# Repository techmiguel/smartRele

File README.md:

# SmartRele · rele-esp12f

**Single-channel Wi-Fi relay module based on the ESP-12F (ESP8266) for 110–120 VAC mains.**

A 2-layer, **66.5 × 49 mm** board that switches a mains load of up to **10 A** from an ESP-12F. It is powered directly from the mains through an isolated HLK-PM01 supply and integrates input protection (time-lag fuse and varistor), a 16 A Omron G5RL power relay, status indicators and a programming header. All components sit on the top side, and the board is ready to be ordered **fully assembled from JLCPCB** (SMD and THT), with no hand soldering.

> [!WARNING]
> This design operates at **mains voltage**. Assembly, testing and installation must be carried out by qualified people. Read the [Safety](#safety) section before connecting the board.

---

## Table of contents
- [Features](#features)
- [Specifications](#specifications)
- [Architecture](#architecture)
- [Connectors and pinout](#connectors-and-pinout)
- [Repository layout](#repository-layout)
- [Manufacturing and assembly](#manufacturing-and-assembly)
- [Firmware](#firmware)
- [First firmware flashing](#first-firmware-flashing)
- [Enclosure](#enclosure)
- [Design verification](#design-verification)
- [Safety](#safety)
- [Documentation](#documentation)
- [License](#license)

## Features
- **ESP-12F** with its PCB antenna overhanging a cut-out in the top-right corner: no copper and no FR-4 below it, as the Espressif hardware design guidelines recommend.
- **Omron G5RL-1A-E-HR relay** (SPST-NO, 16 A / 250 VAC) with 8 mm coil-to-contact separation (reinforced insulation per the manufacturer).
- **Strict mains / low-voltage zoning** enforced by custom design rules: 4 mm between mains and low voltage, 2 mm between mains nets. Measured minimum clearance: 4.35 mm.
- **Duplicated power path** on both sides (2 × 2.5 mm, 35 µm), sized for 10 A with a ~12 °C temperature rise (IPC-2221).
- **Input protection**: T500mA time-lag fuse (protects the supply) and 07D221K varistor.
- **Robust start-up**: RC delay on EN and RST, 10 µF + 100 nF decoupling next to the module, and the relay held open during reset.
- **Indicators** for relay (red) and Wi-Fi (blue); user/boot (GPIO0) and reset push buttons.
- **Programming** through a 2×3 header powered at 5 V; OTA updates afterwards.
- **Complete manufacturing package**: Gerbers, drill files, BOM and CPL ready for JLCPCB, with 3D models for every part.
- **3D-printable enclosure**, parametric and checked against the 3D model of the assembled board.

## Specifications

| Parameter | Value |
|---|---|
| Input voltage | 110–120 VAC, 50/60 Hz |
| Maximum load | 10 A resistive (trace limit; relay 16 A, terminal block 18 A) |
| Contact | SPST-NO, switches the line (L) |
| On-board supply | HLK-PM01, 5 V / 600 mA, isolated |
| Regulator | AMS1117-3.3 |
| Microcontroller | ESP8266 (ESP-12F module), Wi-Fi 802.11 b/g/n |
| Protection | F1 T500mA 250 V (supply branch) · RV1 07D221K |
| PCB | 66.5 × 49 × 1.6 mm, 2 layers, 35 µm copper; 7.6 × 18.7 mm cut-out under the antenna |
| Assembly | Single-sided; 32 components, all factory-assembled |
| Mounting holes | 2 × M2 (MH1, MH2), in the low-voltage zone |

The full datasheet, with test conditions and the source of each value, is in [`docs/rele-esp12f_datasheet_user_guide.pdf`](docs/rele-esp12f_datasheet_user_guide.pdf).

## Architecture

```
 Power      J1:L ──────────► K1 contact (COM → NO) ──────────► J1:OUT ──► load

 Supply     J1:L ── F1 ── L_F ──► PS1 HLK-PM01 ──► +5 V ── U1 AMS1117 ──► +3.3 V ──► U2 ESP-12F
                          RV1 between L_F and N

 Control    +5 V ── K1 coil (D1 flyback diode) ── Q1 SS8050 ── GND
                                                   ▲
                                        GPIO5 (U2) ── R6 1 kΩ
```

- **Mains zone** (bottom left): J1, F1, RV1, K1 and the PS1 input.
- **Low-voltage zone** (right): U1 and its capacitors, relay driver, LEDs, push buttons, J3 and mounting holes. GND planes on both sides, restricted to this zone.
- **Top strip**: PS1 on the left and the ESP-12F with its antenna over the corner cut-out on the right edge.

The full schematic is in [`docs/schematic.pdf`](docs/schematic.pdf).

## Connectors and pinout

### J1 — Mains terminal block (3 poles, 5.08 mm pitch)
| Pin | Signal | Function |
|:-:|---|---|
| 1 | N | Neutral |
| 2 | OUT | Switched output to the load |
| 3 | L | Line input |

### J3 — Programming (2×3 header, 2.54 mm pitch)
```
 IO0   TX   GND(1)
 RST   RX   5V
```
Pin 1 (square pad) = GND; pin 2 = 5 V. Labeled on the silkscreen.

### ESP-12F
| GPIO | Function |
|---|---|
| GPIO5 | Relay (SS8050, R6 1 kΩ, R7 10 kΩ to GND) and relay LED (D2) |
| GPIO4 | Wi-Fi LED (D3) |
| GPIO0 | Push button SW1 (flashing mode / application use), 10 kΩ to 3.3 V |
| GPIO2 | 10 kΩ to 3.3 V (boot strap) |
| GPIO15 | 10 kΩ to GND (boot strap) |
| EN, RST | 10 kΩ to 3.3 V + 100 nF to GND; RST also to SW2 |

## Repository layout

```
.
├── rele-esp12f.kicad_pro      KiCad 10 project
├── rele-esp12f.kicad_sch      Schematic
├── rele-esp12f.kicad_pcb      PCB layout
├── rele-esp12f.kicad_dru      Custom design rules (mains isolation)
├── 3dmodels/                  STEP models missing from the KiCad library (K1, F1, SW1/SW2)
├── fabrication/               Production package for JLCPCB
│   ├── gerbers/               Gerbers and drill files (Excellon)
│   ├── gerbers_JLCPCB.zip     Gerbers + drill files + CPL, ready to upload
│   ├── BOM_JLCPCB.csv         Bill of materials with LCSC part numbers
│   └── CPL_JLCPCB.csv         Component placement list
├── docs/
│   ├── schematic.pdf
│   ├── rele-esp12f_datasheet_user_guide.pdf
│   ├── pcb_top.png · pcb_bottom.png
│   └── datasheets/            Datasheets of the key components
├── firmware/                  ESP8266 firmware (PlatformIO, Arduino core)
├── enclosure/                 3D-printable enclosure (FreeCAD, STEP, STL)
├── scripts/                   PDF datasheet generator
├── CHANGELOG.md
└── LICENSE
```

The custom 3D models are referenced through `${KIPRJMOD}/3dmodels/`, so the project opens without any extra path configuration.

## Manufacturing and assembly

1. Upload [`fabrication/gerbers_JLCPCB.zip`](fabrication/gerbers_JLCPCB.zip) to JLCPCB (2 layers, 1.6 mm).
2. Enable **PCB Assembly** (top side) and upload [`BOM_JLCPCB.csv`](fabrication/BOM_JLCPCB.csv) and [`CPL_JLCPCB.csv`](fabrication/CPL_JLCPCB.csv).
3. Before paying, check in the JLCPCB viewer that:
   - U2 and K1 sit on their pads;
   - the J1 wire entry faces the board edge;
   - J3 pin 1 lands on the square pad (GND);
   - every BOM line has a part selected.

THT parts are wave-soldered. The CPL uses the **pad center** (JLCPCB convention), not the body center; for U2 and K1 they differ. The drill holes of J1 (Ø1.5 mm) and RV1 (Ø1.0 mm) are matched to the actual parts.

### Power and THT components

| Ref. | Part | LCSC | Notes |
|---|---|---|---|
| PS1 | Hi-Link HLK-PM01 | C209903 | Isolated 5 V supply |
| K1 | Omron G5RL-1A-E-HR DC5 | C113250 | SPST-NO 16 A; 5 V coil, 80 mA |
| F1 | Reomax MTS0500A, T500mA 250 V | C2762401 | Time-lag, due to the PS1 inrush current |
| RV1 | Varistor 07D221K | C49072913 | For 110–120 VAC |
| C1 | 470 µF 10 V | C112505 | |
| J1 | KANGNEX WJ500V-5.08-3P | C72334 | 250 V / 18 A |
| J3 | 2×3 header, 2.54 mm | C65114 | Only used for the first flashing |

The full list is in the [BOM](fabrication/BOM_JLCPCB.csv).

### Regenerating the production files

With `kicad-cli` (KiCad 10), from the repository root:

```bash
kicad-cli pcb export gerbers --layers F.Cu,B.Cu,F.SilkS,B.SilkS,F.Mask,B.Mask,F.Paste,Edge.Cuts -o fabrication/gerbers/ rele-esp12f.kicad_pcb
```

```bash
kicad-cli pcb export drill --format excellon --excellon-units mm --excellon-separate-th --excellon-zeros-format decimal -o fabrication/gerbers/ rele-esp12f.kicad_pcb
```

```bash
kicad-cli pcb render --side top -w 1592 -h 904 --background opaque --quality basic --zoom 0.9954 -o docs/pcb_top.png rele-esp12f.kicad_pcb
```

```bash
kicad-cli pcb render --side bottom -w 1592 -h 904 --background opaque --quality basic --zoom 0.9954 -o docs/pcb_bottom.png rele-esp12f.kicad_pcb
```

These explicit options are needed because the plot settings stored in the board produce `.gbr` extensions and an unnecessary B.Paste layer. The ZIP contains the 11 files in `fabrication/gerbers/` plus `CPL_JLCPCB.csv`.

## Firmware

The [`firmware/`](firmware/) folder holds the board's own firmware (PlatformIO, Arduino core for ESP8266). The relay is controlled over Wi-Fi from a built-in web page or a JSON REST API, and from anywhere on the Internet through a Telegram bot:

- manual on / off;
- state-change timer (turn on, off or toggle after 1 s – 7 days);
- cyclic ON/OFF routine (on for one period, off for another, repeated);
- up to 16 weekly schedules synchronised over NTP, with a configurable time zone;
- Telegram bot (optional): remote control and notifications with no server and no port forwarding, so it also works on a phone hotspot or behind CGNAT.

On first boot it opens the `SmartRele-XXXXXX` setup access point; holding SW1 for 8 s erases the Wi-Fi settings. Setup, behaviour, API and security notes are in [`firmware/README.md`](firmware/README.md).

## First firmware flashing

1. **Disconnect the board from mains.**
2. Connect a USB-serial adapter with **3.3 V logic** to J3: TX↔RX, RX↔TX, GND, and its **5 V (VBUS)** output to the 5V pin.
3. Hold SW1 (GPIO0) while pressing and releasing SW2 (RST) to enter flashing mode.
4. Flash the firmware (`pio run -e esp12f -t upload` from `firmware/`). Later updates are done over the air (OTA).

J3 is powered at 5 V rather than 3.3 V for two reasons. The internal output-to-input diode of the AMS1117 would make the adapter also feed the 5 V rail. In addition, the 3.3 V pin of a typical adapter cannot supply the current peaks the ESP8266 draws while calibrating its radio.

Third-party firmware also works: the [datasheet](docs/rele-esp12f_datasheet_user_guide.pdf) includes example configurations for Tasmota and ESPHome.

## Enclosure

The [`enclosure/`](enclosure/) folder contains a two-part enclosure (base and screwed lid) for 3D printing in PETG or ASA/ABS. It is generated by a parametric FreeCAD script, and its interference with the 3D model of the assembled board is zero. Design, printing and assembly details are in [`enclosure/README.md`](enclosure/README.md).

## Design verification

Results with `kicad-cli` 10.0.5, with all zones refilled:

| Check | Errors | Warnings | Warning details |
|---|:-:|:-:|---|
| DRC | **0** | 31 | 23 footprints modified from the library (J1/RV1 drills and custom 3D models; pads otherwise identical); 8 silkscreen items clipped by the edge (PS1/J1 at the rounded corners, U2 outline over the antenna cut-out) |
| Schematic ↔ PCB parity | **0** | 0 | |
| ERC | **0** | 6 | Embedded symbols that differ from the KiCad 10 library (pinout checked against the datasheets) |
| Unconnected pads | **0** | — | |

None of the warnings affects manufacturing. The [kicad-verify](https://github.com/techmiguel/kicad-verify) gate (`verification/pcb/`) also checks the pinout of U1, U2, Q1, PS1, K1 and D1 against their datasheets, the mounting holes against the enclosure, and the consistency of the Gerbers, drill files, BOM and CPL with the board. Measured clearances: mains copper ↔ low voltage ≥ 4.35 mm on both sides; mains copper ↔ board edge ≥ 2.0 mm.

## Safety

- **110–120 VAC mains.** The 07D221K varistor is rated for that voltage. For 230 VAC it must be replaced (e.g. with a 07D471K). F1 is suitable for both voltages.
- **The load current does not flow through F1**, which only protects the supply. Install a circuit breaker or fuse of **≤ 10 A** upstream, dedicated to this output. An on-board fuse would not have enough breaking capacity for a mains short circuit.
- **Never connect J3 while the board is connected to mains.**
- Mount the board in an **insulating enclosure**: mains copper is 2 mm from the board edge.
- Use only **MH1 and MH2** (low-voltage zone) for metal hardware: M2 screws with a head or washer of Ø ≤ 5 mm.
- The printed enclosure provides mechanical and contact protection, but it is **not certified**. For a permanent installation, print it in a flame-retardant material or place it inside an approved electrical junction box.

## Documentation

| Document | Contents |
|---|---|
| [Datasheet and user guide](docs/rele-esp12f_datasheet_user_guide.pdf) | Specifications, operation, installation and design rationale |
| [Schematic](docs/schematic.pdf) | Full schematic in PDF |
| [Datasheets](docs/datasheets/) | Omron G5RL, AMS1117, ESP8266EX, ESP-WROOM-02 and the Espressif hardware design guidelines |
| [Changelog](CHANGELOG.md) | Hardware revisions and the rationale behind each change |
| [Enclosure](enclosure/README.md) | Enclosure design, printing and assembly |

The datasheet is regenerated with `python scripts/generate_datasheet.py` (requires ReportLab, PyMuPDF, Pillow and `kicad-cli`).

## License

Hardware released under the **CERN Open Hardware Licence v2 – Weakly Reciprocal** ([CERN-OHL-W-2.0](LICENSE)).

Inspired by [aman983/ESP-01S_Relay_Module](https://github.com/aman983/ESP-01S_Relay_Module). This is a new design and contains no files from the original.

---

© 2026 [@techmigue](https://github.com/techmiguel)

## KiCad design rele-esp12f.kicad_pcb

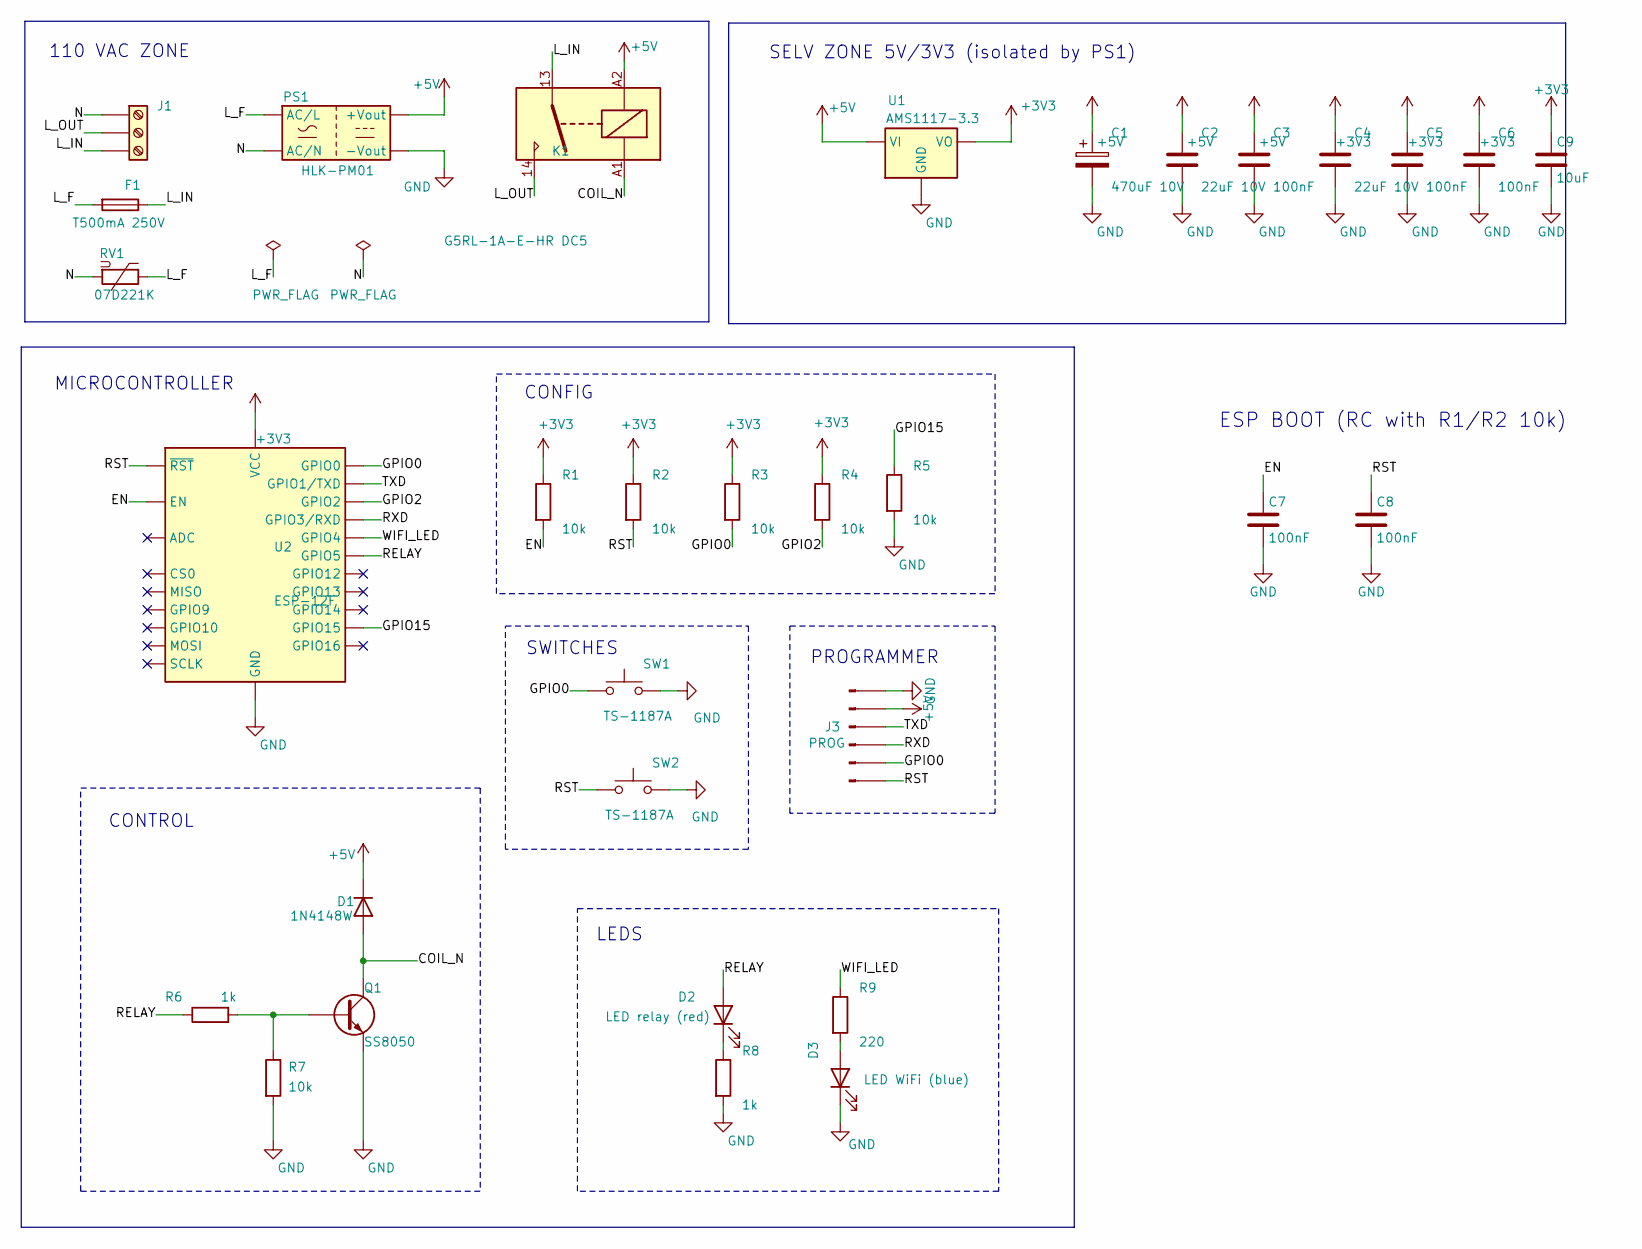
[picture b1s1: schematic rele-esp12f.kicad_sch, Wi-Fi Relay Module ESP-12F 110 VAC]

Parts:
C1: 470uF 10V; CP_Radial_D6.3mm_P2.50mm; MPN ERR1AM471E11OT; LCSC C112505
C2, C4: 22uF 10V; C_0805_2012Metric; MPN CL21A226MAQNNNE; LCSC C45783
C3, C5, C6, C7, C8: 100nF; C_0603_1608Metric; MPN CC0603KRX7R9BB104; LCSC C14663
C9: 10uF; C_0603_1608Metric; MPN CL10A106KP8NNNC; LCSC C19702
D1: 1N4148W; D_SOD-123; MPN 1N4148W; LCSC C81598
D2: LED relay (red); LED_0603_1608Metric; MPN KT-0603R; LCSC C2286
D3: LED WiFi (blue); LED_0603_1608Metric; MPN GL0603UB01; LCSC C51933294
F1: T500mA 250V; Fuse_Littelfuse_395Series; MPN MTS0500A; LCSC C2762401
J1: N / L_OUT / L_IN; TerminalBlock_Phoenix_MKDS-1,5-3-5.08_1x03_P5.08mm_Horizont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; MPN WJ500V-5.08-03P-14-00A; LCSC C72334
J3: PROG; PinHeader_2x03_P2.54mm_Vertical; MPN 2.54-2*3P Pin header; LCSC C65114
K1: G5RL-1A-E-HR DC5; Relay_SPST_Omron_G2RL-1A-E; MPN G5RL-1A-E-HR DC5; LCSC C113250
PS1: HLK-PM01; Converter_ACDC_Hi-Link_HLK-PMxx; MPN HLK-PM01; LCSC C209903
Q1: SS8050; SOT-23; MPN SS8050; LCSC C2150
R1, R2, R3, R4, R5, R7: 10k; R_0603_1608Metric; MPN 0603WAF1002T5E; LCSC C25804
R6, R8: 1k; R_0603_1608Metric; MPN 0603WAF1001T5E; LCSC C21190
R9: 220; R_0603_1608Metric; MPN 0603WAF2200T5E; LCSC C22962
RV1: 07D221K; RV_Disc_D7mm_W3.4mm_P5mm; MPN 07D221K; LCSC C49072913
SW1, SW2: TS-1187A; SW_Push_1P1T_XKB_TS-1187A; MPN TS-1187A-B-A-B; LCSC C318884
U1: AMS1117-3.3; SOT-223-3_TabPin2; MPN AMS1117-3.3; LCSC C6186
U2: ESP-12F; ESP-12E; MPN ESP-12F; LCSC C82891

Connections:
+3V3: C4.1, C5.1, C6.1, C9.1, R1.1, R2.1, R3.1, R4.1, U1.2 (VO), U2.8 (VCC)
+5V: C1.1, C2.1, C3.1, D1.1 (K), J3.2, K1.A2, PS1.4 (+Vout), U1.3 (VI)
/COIL_N: D1.2 (A), K1.A1, Q1.3 (C)
/EN: C7.1, R1.2, U2.3 (EN)
/GPIO0: J3.5, R3.2, SW1.1, U2.18 (GPIO0)
/GPIO2: R4.2, U2.17 (GPIO2)
/GPIO15: R5.1, U2.16 (GPIO15)
/L_F: F1.2, PS1.1 (AC/L), RV1.1
/L_IN: F1.1, J1.3, K1.13
/L_OUT: J1.2, K1.14
/N: J1.1, PS1.2 (AC/N), RV1.2
/RELAY: D2.2 (A), R6.1, U2.20 (GPIO5)
/RST: C8.1, J3.6, R2.2, SW2.1, U2.1 (~RST)
/RXD: J3.4, U2.21 (GPIO3/RXD)
/TXD: J3.3, U2.22 (GPIO1/TXD)
/WIFI_LED: R9.1, U2.19 (GPIO4)
GND: C1.2, C2.2, C3.2, C4.2, C5.2, C6.2, C7.2, C8.2, C9.2, D3.1 (K), J3.1, PS1.3 (-Vout), Q1.2 (E), R5.2, R7.2, R8.2, SW1.2, SW2.2, U1.1 (GND), U2.15 (GND)
unnamed: D2.1 (K), R8.1
unnamed: D3.2 (A), R9.2
unnamed: Q1.1 (B), R6.2, R7.1

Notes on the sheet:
PROGRAMMER
MICROCONTROLLER
110 VAC ZONE
CONFIG
SELV ZONE 5V/3V3 (isolated by PS1)
LEDS
SWITCHES
CONTROL
ESP BOOT (RC with R1/R2 10k)

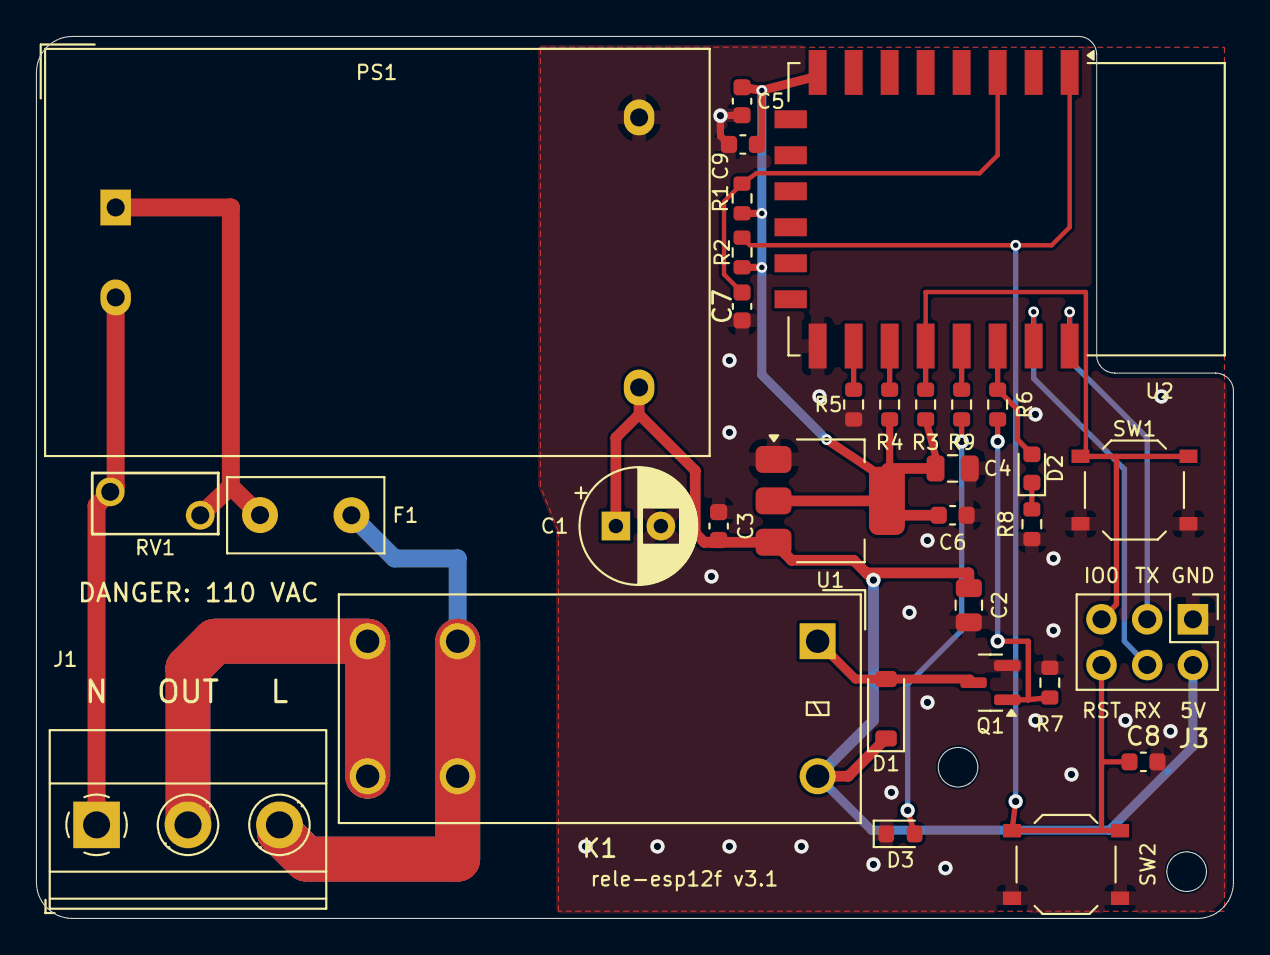
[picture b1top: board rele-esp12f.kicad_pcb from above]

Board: 2 copper layers, 66.5 x 49.0 mm, 34 parts (0 on the bottom side), 20 nets.

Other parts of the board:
MH1, MH2: M2; MountingHole_2.2mm_M2

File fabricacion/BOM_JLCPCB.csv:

Comment,Designator,Footprint,LCSC Part #
22uF 10V,"C2,C4",C_0805_2012Metric,C45783
10uF 10V X5R,C9,C_0603_1608Metric,C19702
100nF,"C3,C5,C6,C7,C8",C_0603_1608Metric,C14663
1N4148W,D1,D_SOD-123,C81598
LED relay (rojo),D2,LED_0603_1608Metric,C2286
LED WiFi (azul),D3,LED_0603_1608Metric,C51933294
SS8050,Q1,SOT-23,C2150
10k,"R1,R2,R3,R4,R5,R7",R_0603_1608Metric,C25804
1k,"R6,R8",R_0603_1608Metric,C21190
220,R9,R_0603_1608Metric,C22962
TS-1187A,"SW1,SW2",SW_Push_1P1T_XKB_TS-1187A,C318884
AMS1117-3.3,U1,SOT-223-3_TabPin2,C6186
470uF 10V,C1,CP_Radial_D6.3mm_P2.50mm,C112505
T500mA 250V (Reomax MTS0500A; time-lag),F1,Fuse_Littelfuse_395Series,C2762401
"G5RL-1A-E-HR DC5 (Omron, 16 A, SPST-NO)",K1,Relay_SPST_Omron_G2RL-1A-E,C113250
HLK-PM01,PS1,Converter_ACDC_Hi-Link_HLK-PMxx,C209903
07D221K,RV1,RV_Disc_D7mm_W3.4mm_P5mm,C49072913
ESP-12F,U2,ESP-12E,C82891
N / L_OUT / L_IN (borna 3P 5.08 mm),J1,"TerminalBlock_Phoenix_MKDS-1,5-3-5.08_1x03_P5.08mm_Horizontal",C72334
PROG (header 2x3 2.54 mm),J3,PinHeader_2x03_P2.54mm_Vertical,C65114

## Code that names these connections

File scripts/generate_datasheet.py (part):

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    arrow(g, [362, 196, 392, 196], ACC)        ; lbl(g, 365, 199, '+3V3', 6.4, ACC)
    arrow(g, [276, 196, 276, 80, 266, 80], ACC); lbl(g, 270, 92, 'coil', 5.8, ACC)
    arrow(g, [292, 62, 266, 62], ACC)          ; lbl(g, 268, 52, 'COIL_N', 5.8, ACC)
    arrow(g, [392, 124, 378, 124, 378, 70, 362, 70], ACC); lbl(g, 380, 96, 'GPIO5', 6.0, ACC)
    arrow(g, [378, 130, 362, 130], ACC)        ; lbl(g, 364, 150, 'GPIO5/4', 5.8, ACC)
    arrow(g, [424, 82, 424, 112], ACC)         ; lbl(g, 427, 92, 'GPIO0 / RST', 5.8, ACC)
    arrow(g, [Wd - 14, 34, Wd - 14, 112], ACC) ; lbl(g, Wd - 17, 70, 'UART', 5.8, ACC, anchor='end')
    d.add(g)
    return d
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        'ESP8266EX: Xtensa L106 CPU at 80/160 MHz, Wi-Fi 802.11 b/g/n, +20 dBm in 802.11b [D].',
        'Safe boot state: the relay stays open during reset and boot (pull-down resistor on the transistor base).',
        'Indicators: red relay-status LED (hardwired) and blue Wi-Fi LED (firmware-controlled).',
        'Local push button SW1 (GPIO0, also used to enter flashing mode) and reset push button SW2.',
        'Programming header J3 (2×3, 2.54 mm) powered at 5 V from the USB-serial adapter; later updates over the air (OTA).',
        '2-layer FR-4 PCB, 1.6 mm, 35 µm copper, 66.5 × 49 mm. All components on the top side.',
    ]))
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        'The on-board resistors select normal boot from flash; SW1 forces UART flashing mode.'))
    A(table([
        ['Pin', 'Net', 'Components', 'Level at boot', 'Effect'],
        ['GPIO15', '/GPIO15', 'R5 10 k to GND', '0', 'Must be 0 to boot from flash or UART.'],
        ['GPIO2', '/GPIO2', 'R4 10 k to 3V3', '1', 'Must be 1.'],
        ['GPIO0', '/GPIO0', 'R3 10 k to 3V3; SW1 to GND; J3-5', '1 (0 with SW1)', '1 = boot from flash; 0 = UART flashing mode.'],
        ['EN (CH_PD)', '/EN', 'R1 10 k to 3V3; C7 100 nF to GND', '↑ with τ = 1 ms', 'Enables the chip once VCC has settled.'],
        ['RST', '/RST', 'R2 10 k to 3V3; C8 100 nF; SW2 to GND; J3-6', '↑ with τ = 1 ms', 'External reset; SW2 restarts the module.'],
    ], [1.4, 1.4, 3.6, 1.8, 4.6]))
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        'after VDD33 (t<sub>3</sub>, t<sub>5</sub> ≥ 0.1 ms [D]). Without capacitors, a slow ramp of the '
        '3.3 V rail can leave the chip in an undefined state.'))
    A(Paragraph('3.4 Relay driver', sH2))
    A(P('GPIO5 (net <font face="Mono">/RELAY</font>) drives the base of Q1 (SS8050, NPN) through R6 (1 kΩ). '
        'Q1 switches the low side of the coil (<font face="Mono">/COIL_N</font>); the other end is at +5 V. '
        'D1 (1N4148W) recirculates the coil current when Q1 turns off and clamps its collector to '
        '≈ 5.7 V. R7 (10 kΩ) holds the base at GND while GPIO5 is high-impedance (reset, boot, '
        'flashing): the relay <b>cannot close</b> until the firmware commands it.'))
    A(table([
        ['Quantity', 'Calculation', 'Result'],
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        ['Base current (V<sub>OH</sub> = 3.3 V)', '(3.3 − 0.75) / 1 k − 0.75 / 10 k', '2.48 mA'],
        ['Base current (V<sub>OH</sub> min. = 2.64 V)', '(2.64 − 0.75) / 1 k − 0.75 / 10 k', '1.82 mA'],
        ['Forced β (worst case)', '80 mA / 1.82 mA', '≈ 44 → saturation with ample margin (SS8050 h<sub>FE</sub> ≫ 44)'],
        ['Total GPIO5 current', 'I<sub>B</sub> + I<sub>D2</sub> ≈ 2.5 + 1.4', '≈ 3.9 mA (< 12 mA [D])'],
    ], [3.3, 4.7, 5]))
    A(P('With a plain parallel diode the coil current decays slowly and the contact opens somewhat later than '
        'the 5 ms in the datasheet (not measured). For a 10 A AC load this is acceptable; a zener in series '
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    A(Paragraph('3.5 Indicators and push buttons', sH2))
    A(table([
        ['Ref.', 'Element', 'Connection', 'Logic', 'Notes'],
        ['D2', 'Red "relay" LED', 'GPIO5 → D2 → R8 1 k → GND', 'Active high', 'In parallel with the driver: on = close command issued. ≈ 1.4 mA [E].'],
        ['D3', 'Blue "Wi-Fi" LED', 'GPIO4 → R9 220 Ω → D3 → GND', 'Active high', 'Meaning defined by the firmware. Current ≈ 1–2 mA, depends on the blue LED V<sub>F</sub> [E].'],
        ['SW1', 'TS-1187A push button', 'GPIO0 ↔ GND', 'Active low', 'Local switching in service; held during reset = flashing mode.'],
        ['SW2', 'TS-1187A push button', 'RST ↔ GND', 'Active low', 'Module reset.'],
    ], [0.8, 2.3, 3.6, 1.6, 5]))
    A(PageBreak())
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        ['2', '+5 V (input)', '5 V / VBUS'],
        ['3', 'ESP TXD', 'adapter RX'],
        ['4', 'ESP RXD', 'adapter TX'],
        ['5', 'GPIO0', 'GND to flash (or use SW1)'],
        ['6', 'RST', 'optional (or use SW2)'],
    ], [1.3, 1.6, 2.6])
    wrap = Table([[jt, jdesc]], colWidths=[75 * mm, W_FULL - 75 * mm])
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    A(Paragraph('4.3 ESP-12F pin assignment', sH2))
    A(table([
        ['Module pin', 'GPIO', 'Net', 'Direction', 'Use'],
        ['20', 'GPIO5', '/RELAY', 'Output', 'Relay K1 (via Q1) and LED D2. Active high.'],
        ['19', 'GPIO4', '/WIFI_LED', 'Output', 'LED D3. Active high.'],
        ['18', 'GPIO0', '/GPIO0', 'Input', 'Push button SW1 (active low, pull-up R3). Strapping pin.'],
        ['22', 'GPIO1 / TXD', '/TXD', 'Output', 'UART0 TX → J3-3. Firmware log at 115,200 bit/s (typical).'],
        ['21', 'GPIO3 / RXD', '/RXD', 'Input', 'UART0 RX ← J3-4.'],
        ['17', 'GPIO2', '/GPIO2', '—', 'Pull-up R4. Strapping pin. Usable by the firmware with care (on many ESP-12F modules it drives the on-module blue LED, active low [F]).'],
        ['16', 'GPIO15', '/GPIO15', '—', 'Pull-down R5. Strapping pin. Do not use.'],
        ['1 · 3', 'RST · EN', '/RST · /EN', 'Input', 'Reset (SW2, J3-6) and enable, with a 1 ms RC.'],
        ['4, 5, 6, 7', 'GPIO16, 14, 12, 13', '—', '—', 'Not connected. Only reachable by soldering to the module castellations.'],
        ['2', 'ADC (TOUT)', '—', '—', 'Not connected.'],
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    A(code('{"NAME":"rele-esp12f","GPIO":[32,0,0,0,544,224,0,0,0,0,0,0,0,0],"FLAG":0,"BASE":18}'))
    A(table([
        ['Position', 'GPIO', 'Code', 'Tasmota function'],
        ['1', 'GPIO0', '32', 'Button1 (SW1)'],
        ['5', 'GPIO4', '544', 'LedLink (D3, shows Wi-Fi/MQTT connection)'],
        ['6', 'GPIO5', '224', 'Relay1 (K1 and D2)'],
        ['others', '—', '0', 'Unused (GPIO1/3 remain the UART for logging)'],
    ], [1.3, 1.3, 1.3, 8]))
    A(P('Recommended console settings: <font face="Mono">PowerOnState 0</font> (relay open after a power '
        'outage) or <font face="Mono">PowerOnState 3</font> (restore the last state), and <font face="Mono">SetOption1 1</font> '
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ota:
  - platform: esphome
status_led:
  pin: GPIO4                    # D3, active high
switch:
  - platform: gpio
    id: relay
    name: "Relay"
    pin: GPIO5                  # Q1 -> K1, and LED D2
    restore_mode: RESTORE_DEFAULT_OFF
binary_sensor:
  - platform: gpio
    name: "Button SW1"
    pin:
      number: GPIO0
      inverted: true            # active low, external pull-up R3
    filters:
      - delayed_on: 30ms        # debounce
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'''))
    A(callout('note', 'Custom firmware (Arduino / PlatformIO)', [
        'Board: "Generic ESP8266 Module" or "NodeMCU 1.0 (ESP-12E)"; 4 MB flash, DOUT or DIO mode.',
        'Configure GPIO5 as an output and write LOW first thing in <font face="Mono">setup()</font>.',
        'Read GPIO0 as a debounced input. Do not use GPIO6–11, and do not turn GPIO15/GPIO2 into outputs that could be left at the wrong level on reset.',
        'Include OTA updates from the first version: once the board is installed, J3 can no longer be used.']))
    A(PageBreak())

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    A(Paragraph('13.1 Indicators', sH2))
    A(table([
        ['Indicator', 'State', 'Meaning'],
        ['Red LED (D2)', 'On', 'The firmware commands the relay to close (GPIO5 high). It is wired in parallel with the driver, so it reflects the command, not the mechanical position of the contact.'],
        ['Red LED (D2)', 'Off', 'Relay open; also during boot and flashing.'],
        ['Blue LED (D3)', 'Firmware-defined', 'Tasmota (LedLink): blinks while looking for Wi-Fi/MQTT, off once connected (configurable with LedState). ESPHome (status_led): blinks on error or warning, off when all is well.'],
        ['Audible click', 'When switching', 'K1 contact closing or opening. If the red LED changes without a click, see §15.'],
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    A(table([
        ['Symptom', 'Probable cause', 'Check / solution'],
        ['With mains: no LED, not visible on the Wi-Fi network', 'F1 open, PS1 faulty, terminal block badly wired or no firmware.', 'Without mains, power from J3: if it works, the fault is in the mains zone (F1, RV1, PS1). Check F1 continuity de-energized.'],
        ['Firmware does not start; the serial console shows "boot mode:(1,x)"', 'GPIO0 low at boot.', 'SW1 stuck or IO0 wire to GND on J3. Release it and press SW2.'],
        ['esptool does not connect ("Failed to connect")', 'Not in flashing mode; TX/RX not crossed; port or drivers.', 'Repeat §10.2; cross TX↔RX; try 115,200 bit/s; check the COM port.'],
        ['Resets when Wi-Fi connects or the relay switches', 'Insufficient supply.', 'Via J3: use the adapter 5 V, not 3.3 V, and a short USB cable. With mains: check C1/C9 and the PS1 output.'],
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

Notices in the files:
README.md:
License: CERN-OHL-W-2.0
rele-esp12f.kicad_sch:
Hardware: CERN-OHL-W v2
scripts/generate_datasheet.py:
mm, 8.3 * mm, 'Hardware CERN-OHL-W v2  ·  Uncertified prototype: see §1.4 and §8')
mm, 14 * mm, 'KiCad 10 project · Hardware CERN-OHL-W v2 · Author: @techmigue')
